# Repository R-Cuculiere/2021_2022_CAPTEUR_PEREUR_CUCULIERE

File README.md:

# 2022_CAPTEUR_Pereur_Cuculière
--------------------------------
## Sommaire

--------------------------------
## Etapes de conception (Générales)

- Design et simulations du circuit d'amplification sous LtSpice
- Implémentation du circuit sous KiCAD et design du PCB
- 

--------------------------------
## Design et simulations du circuit analogique - SHIELD

--------------------------------
## Conception du SHIELD sous KiCAD

Nous avons commencé par le l'implémentation de l'amplificateur transimpédance dans le schéma électrique global du SHIELD visible ci-dessous : 

Nous avons ensuite procédé au routage du PCB : 

Routage

Visualisation 3D

--------------------------------
## Développement du programme Arduino

--------------------------------
## Banc de tests

--------------------------------
## Création de la datasheet

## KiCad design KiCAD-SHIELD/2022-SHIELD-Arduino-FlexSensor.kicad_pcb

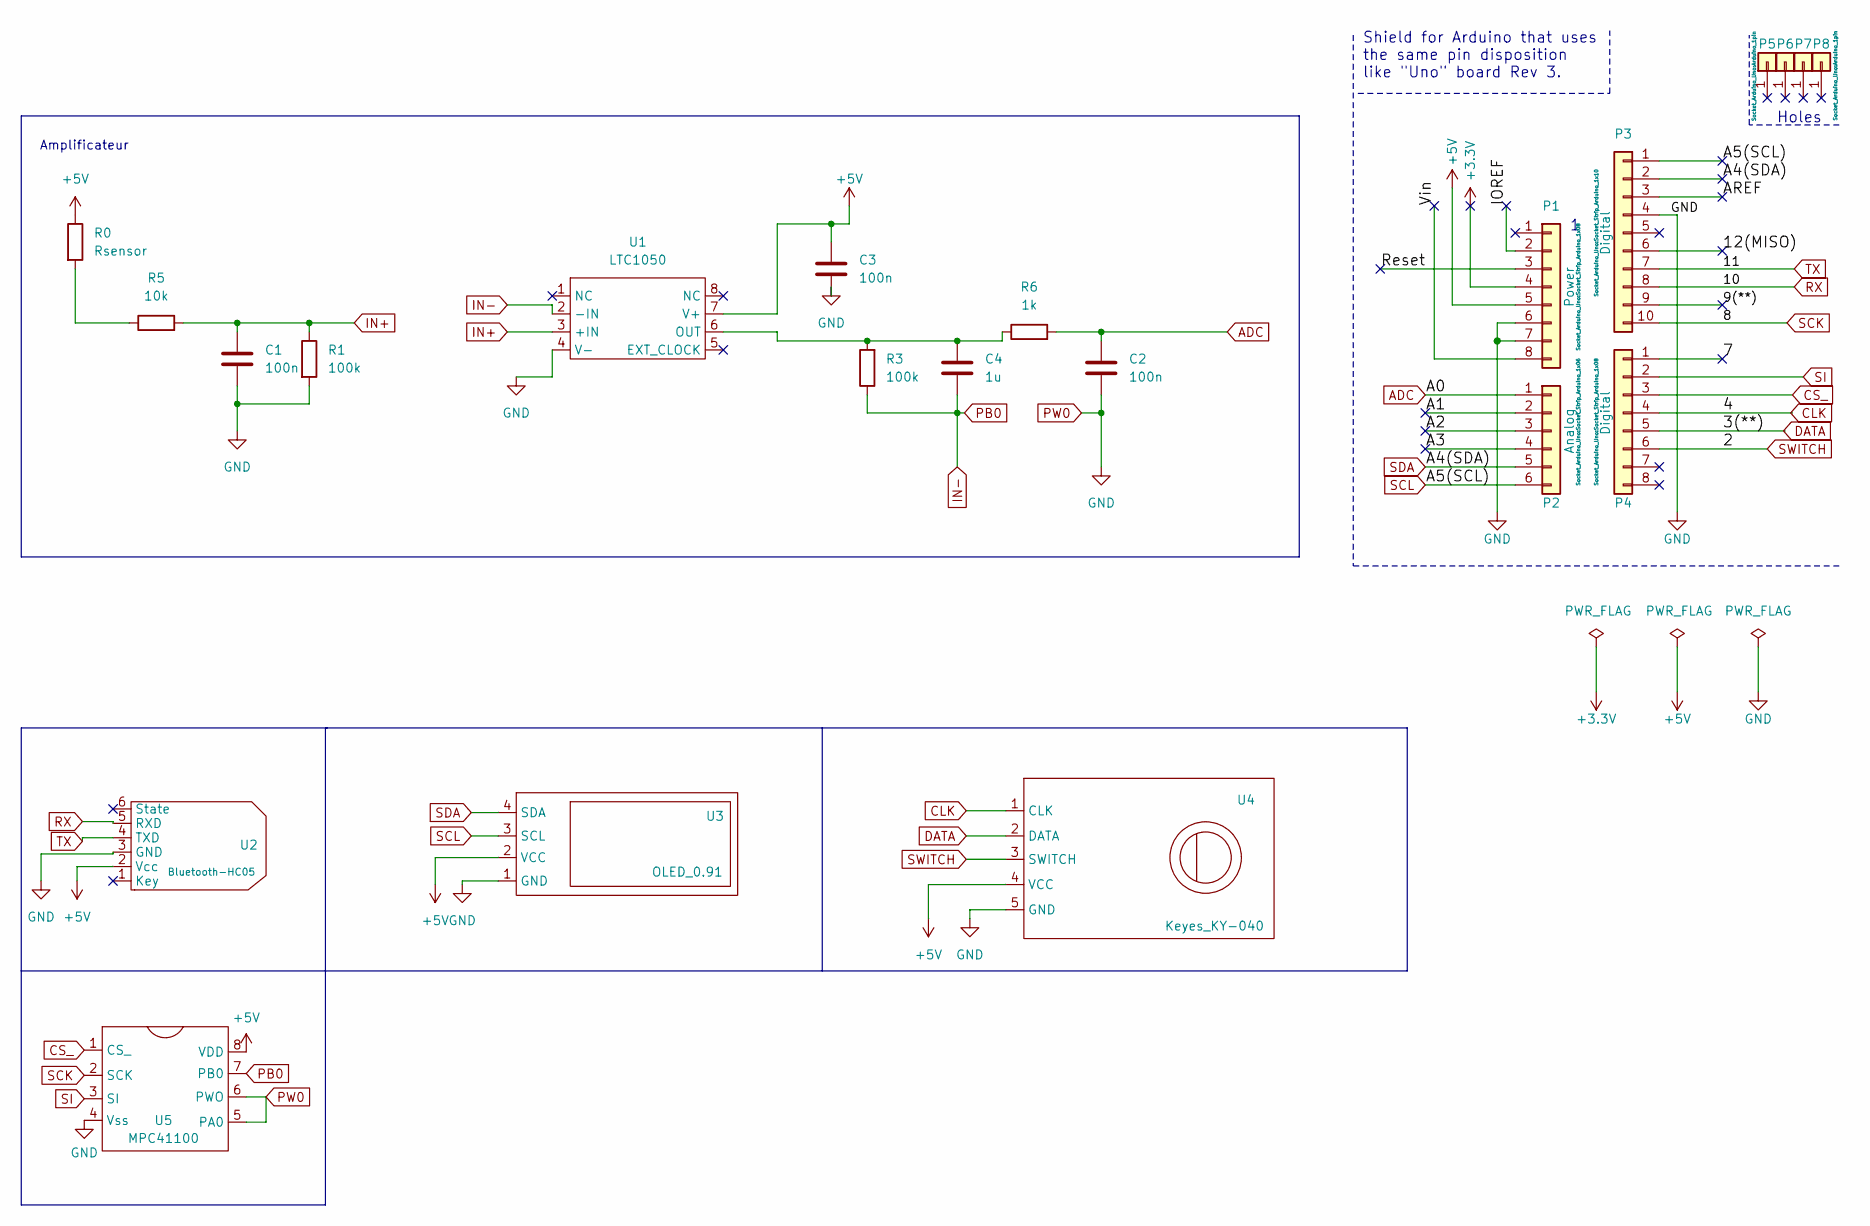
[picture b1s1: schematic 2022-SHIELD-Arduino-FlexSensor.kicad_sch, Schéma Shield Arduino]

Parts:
C1, C3: 100n; C_Disc_D4.3mm_W1.9mm_P5.00mm
C2: 100n; C_Disc_D7.5mm_W5.0mm_P7.50mm
C4: 1u; C_Rect_L7.0mm_W4.5mm_P5.00mm
P1: Power; Socket_Strip_Arduino_1x08
P2: Analog; Socket_Strip_Arduino_1x06
P3: Digital; Socket_Strip_Arduino_1x10
P4: Digital; Socket_Strip_Arduino_1x08
P5, P6, P7, P8: CONN_01X01; Arduino_1pin
R0: Rsensor
R1, R3: 100k; R_Axial_DIN0207_L6.3mm_D2.5mm_P7.62mm_Horizontal
R5: 10k; R_Axial_DIN0207_L6.3mm_D2.5mm_P7.62mm_Horizontal
R6: 1k; R_Axial_DIN0204_L3.6mm_D1.6mm_P7.62mm_Horizontal
U1: LTC1050
U2: Bluetooth-HC05; HC-05
U3: OLED_0.91; SIP-4
U4: Keyes_KY-040; KY-040
U5: MPC41100; MPC41100_FP

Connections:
+3V3: P1.4
+5V: C3.1, P1.5, R0.1, U1.7 (V+), U2.2 (Vcc), U3.2 (VCC), U4.4 (VCC), U5.8 (VDD)
/7: P4.1
/9(**): P3.9
/12(MISO): P3.6
/A1: P2.2
/A2: P2.3
/A3: P2.4
/AREF: P3.3
/IOREF: P1.2
/Reset: P1.3
/Vin: P1.8
ADC: C2.1, P2.1, R6.2
CLK: P4.4, U4.1 (CLK)
CS_: P4.3, U5.1 (CS_)
DATA: P4.5, U4.2 (DATA)
IN+: C1.1, R1.1, R5.2, U1.3 (+IN)
IN-: C4.2, R3.1, U1.2 (-IN), U5.7 (PB0)
unnamed: C4.1, R3.2, R6.1, U1.6 (OUT)
unnamed: R0.2, R5.1
RX: P3.8, U2.5 (RXD)
SCK: P3.10, U5.2 (SCK)
SCL: P2.6, P3.1, U3.3 (SCL)
SDA: P2.5, P3.2, U3.4 (SDA)
SI: P4.2, U5.3 (SI)
SWITCH: P4.6, U4.3 (SWITCH)
TX: P3.7, U2.4 (TXD)

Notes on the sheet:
Holes
Shield for Arduino that uses the same pin disposition like "Uno" board Rev 3.
Amplificateur

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
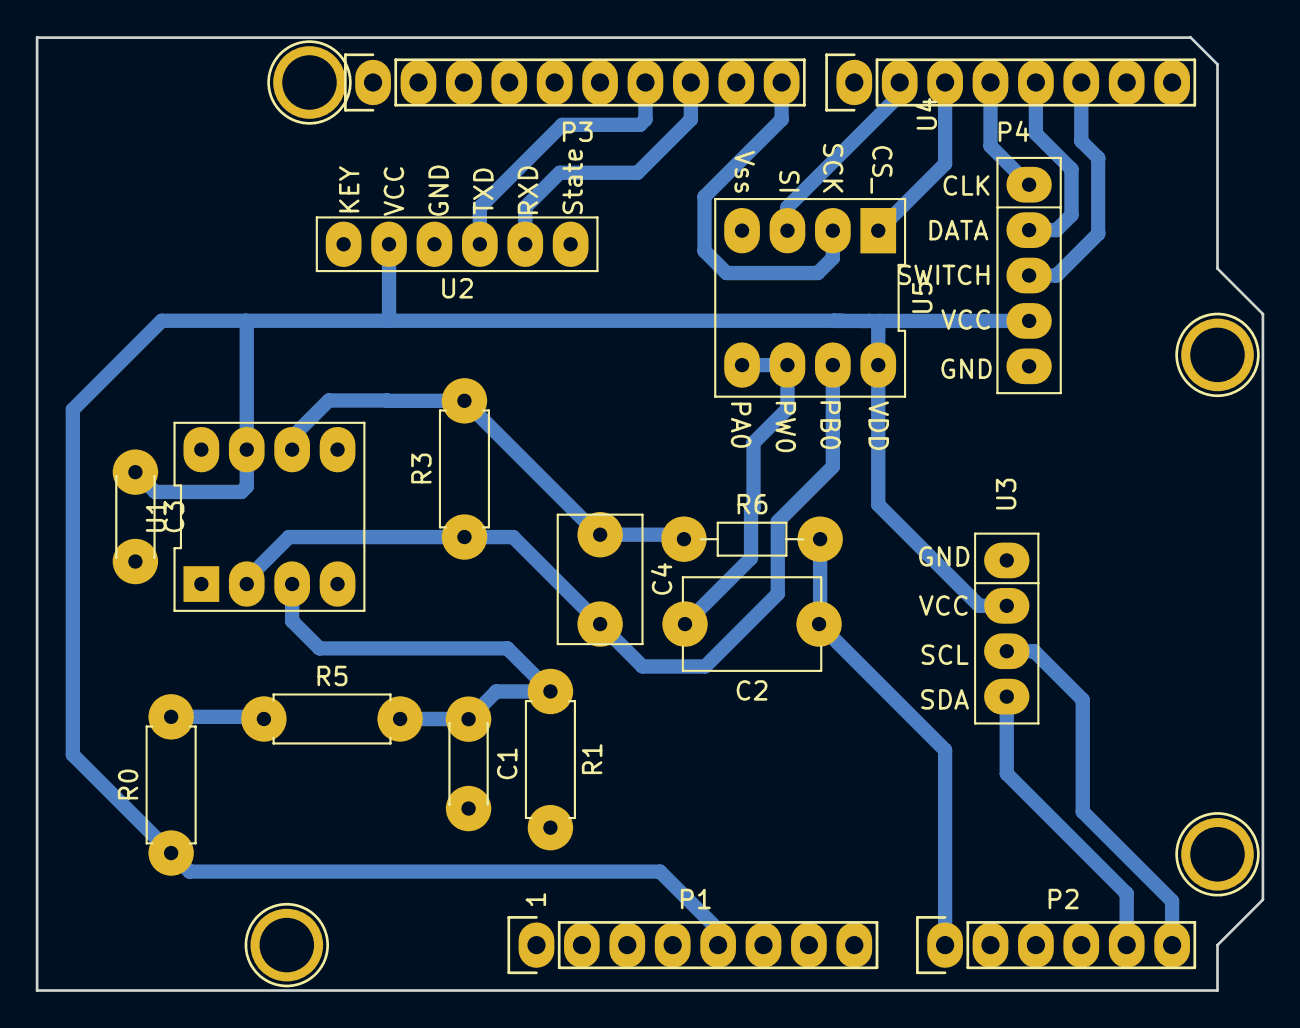
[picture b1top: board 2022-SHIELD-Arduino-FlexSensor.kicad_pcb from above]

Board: 2 copper layers, 68.6 x 53.3 mm, 22 parts (0 on the bottom side), 18 nets.

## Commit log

2022-02-11 1st Commit
    Création du fichier README.md
2022-02-11 2nd Commit
    Création PGM_arduino & .gitignore
    2nd Commit
    Création PGM_arduino & .gitignore
2022-02-11 Modif gitignore et pgm capteur
2022-02-11 modif readme
2022-02-11 test modif 2
2022-03-08 Create SHIELD
2022-04-01 PGM Arduino
2022-04-06 Changement nom directory
2022-04-08 Rajout partie électronique analogique
    Création et simulation de l'amplificateur relié au capteur sous LtSPICE
2022-04-10 Add and change in electronic
